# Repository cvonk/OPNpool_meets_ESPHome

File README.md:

> OPNpool Meets ESPHome has been merged with my [original OPNpool](https://github.com/cvonk/OPNpool) repo.  Please refer to that repo instead.

Ever dreamed of making your pool smarter and easier to manage? If you’ve ever owned a backyard pool, you know it’s not just about swimming—there’s a whole world of chemicals, covers, vacuums, brushes, and fiddling with thermostats and circuits. Even with a saltwater pool, you’ve got to keep a close eye on things!

Enter OPNpool: your pool’s new best friend. It takes all the classic pool controller features and brings them into your smart home. OPNpool keeps track of your controller, pump, and chlorinator, so you don’t have to run outside every time you want to check or change something. Even better, you can set up automations—like running the pump longer when it’s hot out—all from the comfort of your phone or smart home dashboard.

Thanks to some clever folks who reverse engineered the RS485 protocol, OPNpool can eavesdrop on the chatter between your pool’s components. The ESP32 inside shares all that state info as JSON/HTTP and can publish it via MQTT. And if you’re a Home Assistant fan, you’ll love how easily it integrates using MQTT Discovery.

# OPNpool meets ESPHome

OPNpool meets ESPHome is an open-source hardware and software solution that brings advanced pool automation to your smart home. By bridging legacy pool controllers with modern IoT platforms, OPNpool enables real-time monitoring, remote control, and seamless integration with Home Assistant. Whether you want to automate your pool pump based on temperature, monitor chlorinator status, or simply enjoy the convenience of remote access, OPNpool provides a robust and extensible platform for pool management.

## How it works

At its core, OPNpool connects an ESP32 microcontroller to your pool controller’s RS-485 bus. The ESP32 runs ESPHome firmware, which translates pool equipment data into Home Assistant entities. This allows you to view and control your pool’s thermostats, pumps, circuits, and chlorinator directly from your smart home dashboard or mobile app. The system is designed for reliability, safety, and ease of installation, with support for over-the-air updates and waterproof enclosures for outdoor use.

## Features

- [x] **Smart Home Integration:** Native support for Home Assistant and ESPHome.
- [x] **Remote Monitoring & Control:** Access your pool’s status and controls from anywhere.
- [x] **Community Driven:** Built on the work of pool automation enthusiasts and reverse engineers.
- [x] **Open Source:** Fully transparent hardware and software—customize and extend as needed.

## Getting started

No prior experience with pool automation or ESPHome is required. The documentation below will guide you through hardware assembly, wiring, firmware installation, and Home Assistant integration. If you have questions or need help, join the project’s GitHub Discussions for community support.

This device was tested with the Pentair SunTouch controller with firmware **2.080** (2013-07-15), connected to an IntelliFlo pump and IntelliChlor saltwater chlorinator.

> This open source and hardware project is intended to comply with the October 2016 exemption to the Digital Millennium Copyright Act allowing "good-faith" testing," in a controlled environment designed to avoid any harm to individuals or to the public.

## Acknowledgements

> We proudly acknowledge the work of reverse engineering pioneers [Joshua Bloch](https://docs.google.com/document/d/1M0KMfXfvbszKeqzu6MUF_7yM6KDHk8cZ5nrH1_OUcAc/edit), [Michael Russe](http://cocoontech.com/forums/files/file/173-pab014sharezip/), and [George Saw](http://cocoontech.com/forums/topic/27864-download-pitzip/). (Drop me a line if I forgot you.)

## Usage

Start with [installing the ESPHome environment](https://esphome.io/guides/installing_esphome/) on a beefy computer. In my case, this cut the compilation time to a minute, compared to half an hour when running it as an add-on to Home Assistant.

In an empty directory, create a `opnpool-1.yaml` configuration file as shown below.
```yaml
substitutions:
  device_name: opnpool-1
  friendly_name: "OPNpool meets ESPHome"
  description: "External component, see https://github.com/cvonk/OPNpool_meets_ESPHome"

esphome:
  name: ${device_name}
  comment: ${description}
  friendly_name: ${friendly_name}

esp32:
  variant: esp32c6          # or esp32     for <= r3 boards
  board: esp32-c6-devkitc-1 # or lolin_d32 for <= r3 boards
  framework:
    type: esp-idf

wifi:
  domain: !secret domain_name # only needed if not on the same subnet
  min_auth_mode: WPA2
  reboot_timeout: 0s
  networks:
  - ssid: !secret wifi_ssid
    password: !secret wifi_password

api:

ota:
  - platform: esphome
    password: !secret ota_password

external_components:
  - source: github://cvonk/OPNpool_meets_ESPHome
    components: [ opnpool ]

logger:
  level: VERBOSE          # build includes ESP_LOGx up to VERBOSE
  initial_level: WARN     # only show up to WARN globally
  logs:
    poolstate_rx: VERBOSE # show decoded messages

opnpool:
  id: opnpool_1
  RS-485:
    tx_pin:  21  # or 26 for <= r3 boards 
    rx_pin:  22  # or 25 for <= r3 boards
    rts_pin: 23  # or 27 for <= r3 boards
```

Specify your own secrets in `secrets.yaml`

```yaml
wifi_ssid: "REDACTED"
wifi_password: "REDACTED"
domain_name: ".iot.example.com" # appended to base fname to create FQDN for OTA updates
ota_password: "REDACTED"
api_encryption_key: "REDACTED"
```

Compile and upload the code using

```bash
esphome run opnpool-1.yaml
```

The first time, you need to upload over USB Serial, but after that you can use over-the-air updates.

In the output, you should see something like:

```text
[16:26:54.983]I (423) boot: Loaded app from partition at offset 0x10000
[16:26:55.024]I (465) boot: Set actual ota_seq=1 in otadata[0]
[16:26:55.029]I (465) boot: Disabling RNG early entropy source...
[16:26:55.268][W][component:333]: api set Warning flag: unspecified
[16:26:55.273][W][component:342]: wifi set Warning flag: scanning for networks
[16:27:01.293][W][component:373]: wifi cleared Warning flag
[16:27:25.143][E][RS-485:108][pool_req_task]: tx_q full
[16:27:55.144][E][RS-485:108][pool_req_task]: tx_q full
```

In the above trace, the `tx_q full` indicates that it can't transmit to the pool controller.

If you haven't already, add the ESPHome integration to Home Assistant.

Under Integrations, you will find now notice that Home Assistant auto discovered your new device.

{: style="display: block; margin-left: auto; margin-right: auto; width:300px;}

Add it, and specify your API key.  Name the device and assign it an area. You should then see the enities although their values are `unknown`.  Time to populate those entities by connecting it to the pool controller ;-)

## Connect

At the core this project is an ESP32 module and a 3.3 Volt RS-485 adapter. You can
breadboard this using:

* Any ESP32 module that has an USB connector and three GPIO pins available.
* Any "Max485 Module TTL". To make it 3.3 Volt compliant, change the chip to a `MAX3485CSA+`. While you're at it, you may as well remove the 10 kΩ pullup resistors (typically labeled `R1` to `R4`).
* A piece of Cat5 ethernet cable to connect to the pool controller.

{: style="display: block; margin-left: auto; margin-right: auto; width:300px;}

If you prefer to make this a more permanent solution, I suggest rolling a printed circuit board and housing it in a IP68 waterproof case with IP68 connectors.  More about this later.

> :warning: **THIS PROJECT IS OFFERED AS IS. IF YOU USE IT YOU ASSUME ALL RISKS. NO WARRANTIES. At the very least, turn off the power while you work on your pool equipment. Be careful, THERE IS ALWAYS A RISK OF BREAKING YOUR POOL EQUIPMENT.**

Understanding the above warning .. the RS-485 header can be found on the back of the control board. There are probably already wires connected that go to the devices such as pump and chlorinator.

{: style="display: block; margin-left: auto; margin-right: auto; width:400px;}

To minimize electromagnetic interference, use a twisted pairs from e.g. CAT-5 cable to connect the `A`/`B` pair to the RS-485 adapter as shown in the table below.

| Controller       | RS-485 adapter | idle state |         
|:-----------------|:--------------:|:-----------|
| `-DATA` (green)  |  `A`           | negative   |
| `+DATA` (yellow) |  `B`           | positive   |

Connect the RS-485 adapter to the ESP32 module.  I also pulled `GPIO#27` down with a 10 k&ohm; resistor, to keep it from transmiting while the ESP32 is booting.

| RS-485 adapter | ESP32 module |
|:---------------|:-------------|
| RO             | `GPIO#25`    |
| DI             | `GPIO#26`    |
| DE and RE      | `GPIO#27`    |
| GND            | `GND`        |

The serial monitor will start to show decoded messages such as:

```json
{CTRL_VERSION_REQ: {}}
{CTRL_VERSION_RESP: {"firmware":"2.80"}}
{CTRL_TIME_REQ: {}}
{CTRL_TIME_RESP: {"tod":{"time":"18:51","date":"2026-01-18"}}}
{CTRL_HEAT_REQ: {}}
{CTRL_HEAT_RESP: {"thermos":{"POOL":{"temp":54,"sp":63,"src":"NONE"},"SPA":{"temp":54,"sp"}
```

> :bulb: If you don't see such messages, make sure you didn't swap the data leads, or oddly enough some people report that they do need to swap the data leads.  To debug the datalink framing, set the `datalink_rx` logger level to `VERBOSE` and build and upload the code again. See futher below.

In Home Assistant the entities should populate, and show on your favorite Lovelace UI.

{: style="display: block; margin-left: auto; margin-right: auto; width:500px}

## PCB

For a robust and weatherproof installation, we recommend building a custom printed circuit board (PCB) to house the ESP32-C6 module, RS-485 adapter, and DC/DC converter. This approach ensures reliable connections, easier mounting, and long-term durability—especially for outdoor or poolside environments.

{: style="display: block; margin-left: auto; margin-right: auto; width:500px}

Note that the photo above is from a rev 1 board.

### Schematic

The hardware design features a buck converter that supplies 5V to the `5V0` pin on the ESP32-C6 DevKitC-1-N8 daughterboard. The scotty diode prevent issues when the board is also powered via USB.

The main data path runs between the RS-485 connector and the ESP32-C6 on the DevKitC-1-N8. An optional termination resistor is included to minimize signal reflections on the RS-485 bus.

### Board Layout

The entire schematic fits comfortably on a compact two-layer PCB. The board was designed using the free version of AutoDesk EAGLE, and all source files — including layout and schematics — are available in the [hardware directory](tree/main/hardware) of this repository.

{: style="display: block; margin-left: auto; margin-right: auto;}

### Bill of materials

| Name        | Description                                              | Suggested mfr/part#        | Price paid
|-------------|----------------------------------------------------------|----------------------------|-----------
| PBC r4      | Printed circuit board                                    | OSHPark                    | [$9.43](https://oshpark.com/)
| Enclosure   | 158x90x60mm ABS Plastic Junction Box, IP65               | *white label*              | [$9.81](https://www.harfington.com/products/p-1159792)
| RS-485_CONN | 5P Plug+socket, 5-pin, 16mm aviation, IP68               | SP16 5P                    | [$3.98](https://www.aliexpress.us/item/2251832722757291.html)
| RS-485-TERM | Fixed terminal block, 4-pin, screwless, 5 mm pitch       | Phoenix-Contact 1862437    | [$2.02](https://www.digikey.com/en/products/detail/phoenix-contact/1862437/6605421)
| ESP32-C6 DevKitC-1-N8 | ESP32-C6 dev board with 8MB flash, based on ESP32-C6-WROOM | ESP32-C6 DevKitC-1-N8      | [$9.00](https://www.digikey.com/en/products/detail/espressif-systems/ESP32-C6-DEVKITC-1-N8/17728861)
| MAX3485     | Maxim MAX3485CSA, RS-485/UART interface IC 3.3V, 8-SOIC  | Analog-Devices MAX3485CSA+T | [$5.64](https://www.digikey.com/en/products/detail/analog-devices-inc-maxim-integrated/MAX3485CSA-T/1703654)
| DC1         | DC/DC Converter R-78E5.0-0.5, 7-28V to 5V, 0.5A, 3-SIP   | RECOM-Power R-78E5.0-0.5   | [$3.30](https://www.digikey.com/en/products/detail/recom-power/R-78E5-0-0-5/2834904?s=N4IgTCBcDaIEoFEDCB5AsgWgAoHsDuApgE4AEcGA7ABwICsAdAAwaP20gC6AvkA)
| D1, D2      | Schottky Diode, 1N5818, 30V, 1A, DO-41                   | Diodes Incorporated 1N5818-T | [$0.30](https://www.digikey.com/en/products/detail/diodes-incorporated/1N5818-T/22054)
| LED1        | LED, Green Clear 571nm, 1206                             | Lite-On LTST-C150KGKT       | [$0.15](https://www.digikey.com/en/products/detail/diodes-incorporated/1N5818-T/22054)
| LED2        | LED, Amber Clear 602nm, 1206                             | Lite-On LTST-C150AKT       | [$0.15](http2s://www.digikey.com/en/products/detail/liteon/LTST-C150AKT/269213?s=N4IgTCBcDaIDIEsAuBTAtAeQHYAI4BUBlfNAYQEYBWABgEEBpfEAXQF8g)
| C1, C2      | Capacitor, 10 µF, 25 V, multi-layer ceramic, 0805        | KEMET C0805C106K3PACTU     | [$0.22](https://www.digikey.com/en/products/detail/kemet/C0805C106K3PACTU/5267604?s=N4IgTCBcDaINIFECyCAqACAwgBgBzYFZMBGbANjgGYAFAQU1QFUQBdAXyA)
| C3          | Capacitor, 0.1 µF, 6.3 V, multi-layer ceramic, 0805      | KEMET C0805C104M3RACTU     | [$0.12](https://www.digikey.com/en/products/detail/kemet/C0805C104M3RACTU/2211748?s=N4IgTCBcDaINIFECyCAqACAwgBgBzYFZMBGbAFiQGYAlAQU1QFUQBdAXyA)
| R1, R2      | Resistor, 68 Ω, 1/8 W, 0805                              | YAGEO RC0805FR-0768RL      | [$0.20](https://www.digikey.com/en/products/detail/yageo/RC0805FR-0768RL/728097?s=N4IgTCBcDaIJoEEDiBRA8gAgEoGEAMAHHgKwBiWAtHgOwBsBWAMiALoC%2BQA)
| R3          | Not stuffed, resistor, 120 Ω, 1/4 W, 0805                | KAO SG73S2ATTD121J         | [$0.00](https://www.digikey.com/en/products/detail/koa-speer-electronics-inc/RK73B2ATTD121J/10236600)
| PCB Screws  | Machine screw, #6-32 x x 3/16", panhead                  | Keystone-Electronics 9306  | [$0.10](https://www.digikey.com/en/products/detail/keystone-electronics/9306/2746085?s=N4IgjCBcpgTB0QGMoDMCGAbAzgUwDQgD2UA2iLAAwCsIAuoQA4AuUIAyswE4CWAdgHMQAX2GFYZEAGlcAT2zMifXAFoAoplxJuSnkmwACAJwBmSgDZ6woA)
| CONN Screws | Machine screw, M2-0.4 x 16 mm, cheese head               | Essentra 50M020040D016     | [$0.28](https://www.digikey.com/en/products/detail/essentra-components/50M020040D016/11639297)
| CONN Nuts   | Hex nut, M2-0.4, nylon                                   | Essentra 04M020040HN       | [$0.15](https://www.digikey.com/en/products/detail/essentra-components/04M020040HN/9677098)

Note that tariffs and shipping will add to the cost.

## Troubleshooting

Not all controller firmwares are created equally.  If you are not using firmware version 2.080, you will need dive down to the byte level and to tweak the network layer.  If you succeed, please send me an pull request, and I will iinclude it in the next release.

To show more (or less) debug information, specify the levels in `opnpoool-1.yaml`

```yaml
logger:
  level: VERBOSE       # build includes ESP_LOGx up to VERBOSE
  initial_level: WARN  # only show up to WARN globally
  logs:
    rs485: WARN
    datalink_rx: WARN
    datalink_tx: WARN
    network_rx: WARN
    network_create: WARN
    pool_task: WARN
    ipc: WARN
    poolstate: WARN
    poolstate_rx: VERBOSE
    opnpool: WARN
    opnpool_climate: WARN
    opnpool_switch: WARN
    opnpool_sensor: WARN
    opnpool_binary_sensor: WARN
    opnpool_text_sensor: WARN
    enum_helpers: WARN
```

For the `logger` component, it is recommended to use the following levels: `WARN`, which shows only warnings and errors; `INFO`, which includes informational messages such as configuration details, warnings, and errors; and `VERBOSE`, which provides very detailed logs, info, warnings, and errors. Be careful not to enable too much logging, as excessive output can negatively impact the connection between Home Assistant and the ESP32-C6.

### Decoding Stack Traces

If your ESP32-C6 crashes and you notice stack traces in the serial log, you can simplify debugging by enabling ESPHome's stack trace decoder. With this feature, exception addresses are automatically translated into human-readable function names and line numbers within your logs.

To activate the stack trace decoder, add the following lines to your YAML configuration:

```yaml
debug:
  update_interval: 5s  # for exception decoding in logs
```

> **Tip:** Detailed crash information will only appear on the serial console (not in the web logs). Be sure to check the serial output for troubleshooting.

# FAQ

**LEDs not blinking with RS-485 connected**

If communication fails, swap the `-DATA` and `+DATA` wires, as standards for these labels vary. 

**Is a controller required?**

This setup ensures that when selling the house, the next owner is not stuck with a "custom" system. They can use the pool conventionally or easily adopt the smart features.  If you're determined to build your own controller, I can recommend Russ Goldin's [nodejs-poolController](https://github.com/tagyoureit/nodejs-poolController/tree/master).

**Will it work with ___ board?**

There are many boards and kits that incorporate the ESP32. I started with the ESP8266, switched to the original ESP32, and use the ESP-C6. At this point it probably runs on any ESP32 flavor board. If you want to try something else, sure feel free the code is written to be portable. Just make sure you use the MAX3485 instead of the TTL-level MAX485.

**My firmware is ___ How do you update SunTouch firmware?**

Instead of taking such a risky step, I recommend enabling `VERBOSE` logging for `datalink_rx` and `network_rx`.  This will visualize the raw bytes received and messages interpretated. Compare that with the structures `network_msg.h`, and update the file as needed.

> Only do this if you very confident with flashing electronics. You risk bricking your pool controller.

Having read the above warning, you can upgrade if your controller is at [version 2.x](https://saturationregion.blogspot.com/2020/01/whats-deal-with-easytouch-versions-1.html). You will need to get a [USBDM JS16](https://www.aliexpress.us/w/wholesale-Freescale-USBDM-Programmer-JS16.html?spm=a2g0o.detail.search.0) programmer, [make](https://www.troublefreepool.com/threads/how-to-perform-firmware-upgrade-on-pentair-controllers.69589/#post-595657) a [JST cable](https://www.aliexpress.us/w/wholesale-5-PCS-JST-1.-25mm-Male-Female-6p.html?spm=a2g0o.detail.search.0) following [the instructions](https://www.troublefreepool.com/threads/how-to-perform-firmware-upgrade-on-pentair-controllers.69589/page-7#post-2021911).

#
I hope this project brings you joy.  Keep in touch through the dicussion forum.

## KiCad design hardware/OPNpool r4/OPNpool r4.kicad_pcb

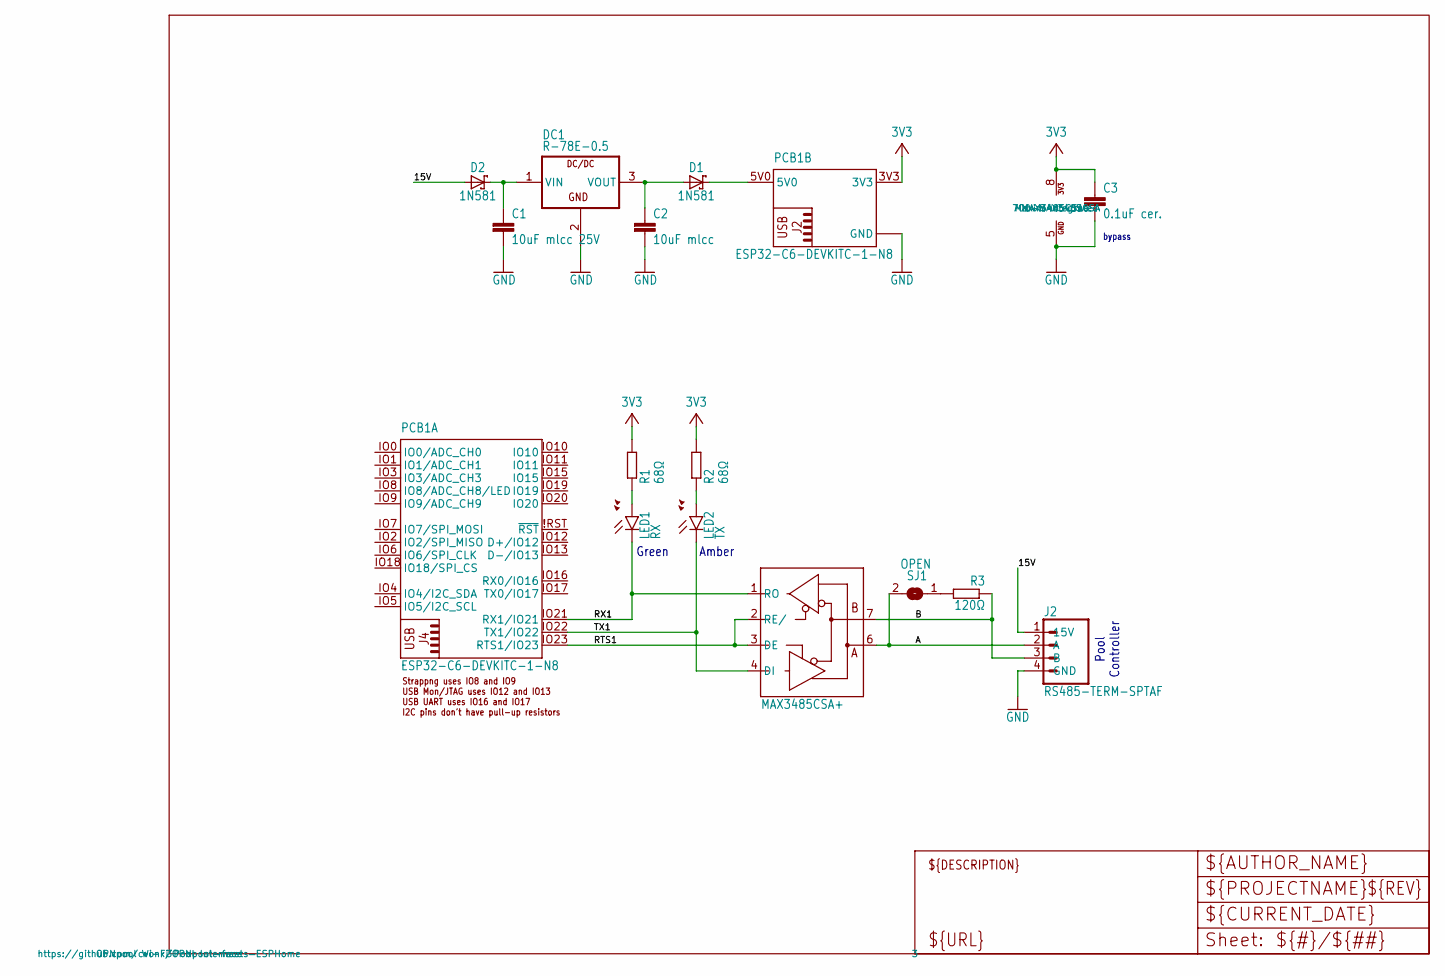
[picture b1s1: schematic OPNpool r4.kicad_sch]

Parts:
C1: 10uF mlcc 25V; C0805K; MOUSER# 81-GJ821BR61E106KE1L
C2: 10uF mlcc; C0805K; MOUSER# 81-GJ821BR61E106KE1L
C3: 0.1uF cer.; C0805K; MOUSER# 80-C0805C104K1REAUTO
D1, D2: 1N581; DO41-7.6; MOUSER# 583-1N5818-T
DC1: R-78E-0.5; SIP3; MOUSER# 919-R-78E5.0-0.5
J2: RS485-TERM-SPTAF; SPTAF1_4-5,0-LL; MOUSER# 651-1864451
LED1: RX; CHIPLED_0805
LED2: TX; CHIPLED_0805
PCB1: ESP32-C6-DEVKITC-1-N8; MODULE_ESP32-C6-DEVKITC-1-N8
R1, R2: 68Ω; R0805; MOUSER# 652-CRM0805JW1R5ELF
R3: 120Ω; R0805; MOUSER# 652-CRM0805JW1R5ELF
SJ1: OPEN; SJ
U1: MAX3485CSA+; SO08; MOUSER# 700-MAX3485CSA

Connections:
3V3: C3.1, PCB1.3V3, R1.2, R2.2, U1.8 (VCC)
15V: D2.A, J2.1 (15V)
A: J2.2 (A), SJ1.2, U1.6 (A)
B: J2.3 (B), R3.1, U1.7 (B)
GND: C1.2, C2.2, C3.2, DC1.2 (GND), J2.4 (GND), PCB1.GND, PCB1.GND@1 (GND), PCB1.GND@2 (GND), PCB1.GND@3 (GND), U1.5 (GND)
unnamed: LED1.A, R1.1
unnamed: LED2.A, R2.1
unnamed: D1.C, PCB1.5V0
unnamed: R3.2, SJ1.1
RTS1: PCB1.IO23 (RTS1/IO23), U1.2 (RE/), U1.3 (DE)
RX1: LED1.C, PCB1.IO21 (RX1/IO21), U1.1 (RO)
TX1: LED2.C, PCB1.IO22 (TX1/IO22), U1.4 (DI)
VIN: C1.1, D2.C, DC1.1 (VIN)
VOUT: C2.1, D1.A, DC1.3 (VOUT)

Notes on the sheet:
bypass
Pool Controller
Green
Amber

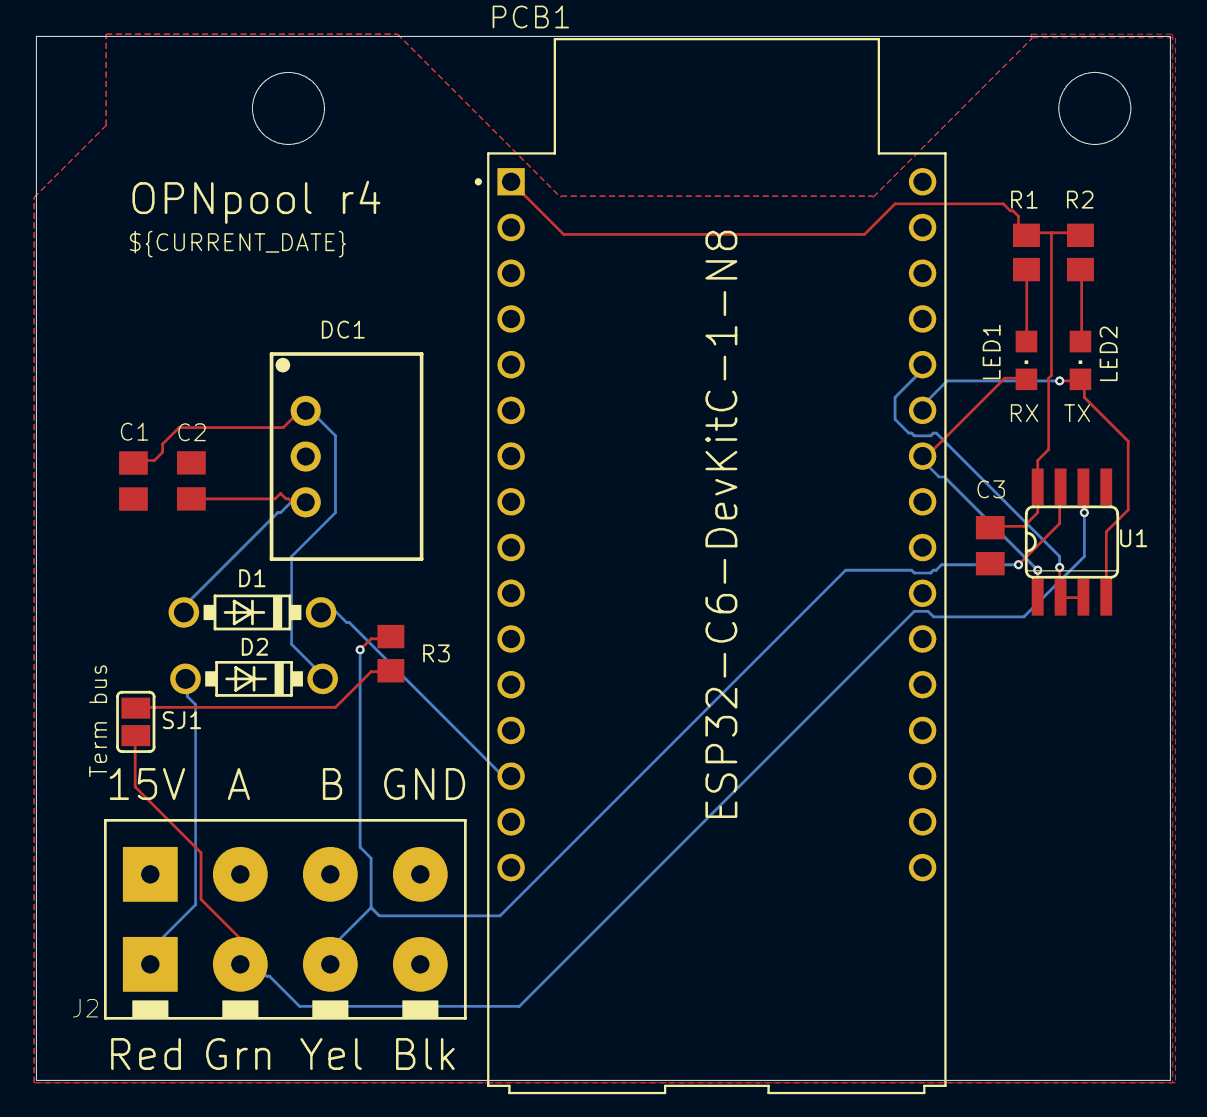
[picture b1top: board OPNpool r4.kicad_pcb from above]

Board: 2 copper layers, 63.0 x 58.0 mm, 17 parts (0 on the bottom side), 14 nets.

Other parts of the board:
UNK_HOLE_0: dummyfp0
UNK_HOLE_1: dummyfp1

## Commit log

2025-12-30 Create README.md for OPNpool project
    Add initial README for OPNpool project with features and setup instructions.
2026-01-03 initial
2026-01-03 add entities
2026-01-03 one more step
2026-01-03 use native UART
2026-01-03 add device class to analog sensors
2026-01-03 add debug levels
2026-01-04 add missing entities
2026-01-04 first bytes received
2026-01-04 group debug keys
2026-01-05 add dbg levels
2026-01-05 Stop tracking __pycache__ directory
2026-01-06 import modules from my regular OPNpool project
2026-01-06 initial msg from pool ctrl
2026-01-06 log msgs from datalink_rx.cpp are now showing up after adding the apparently missing #include "esphome/core/log.h"
2026-01-06 move debug settings to logger
2026-01-06 refractor
2026-01-06 fix crash in case IPC_TO_HOME_TYP_PUBLISH_DATA_DBG
2026-01-07 prevent *(null) read, by change network_msg_t to have a bytes[0] member instead of *bytes.
2026-01-07 prep for moving poolstate to home_task
2026-01-07 add doxygen blocks for skb
2026-01-07 fix skb_pull()
2026-01-08 use correct include paths to help intilisense
2026-01-08 make network_msg the interface between the home and pool tasks
2026-01-08 fix compile err
2026-01-08 fix debug statements
2026-01-08 Initial plan
2026-01-08 Implement IPC switch command forwarding to pool_task
    - Extended OpnPoolSwitch with parent pointer and circuit_id
    - Implemented OpnPool::on_switch_command() to allocate and send network_msg_ctrl_circuit_set_t via IPC
    - Updated pool_task to handle MSG_TYP_CTRL_CIRCUIT_SET messages and convert to datalink packets
    - Wired up switches in __init__.py with parent and circuit_id mapping
2026-01-08 Add initial README for OPNpool porting project
2026-01-08 Update README with project link for OPNpool
2026-01-09 undo a bunch of Copilot PR. First time setting circuit works
2026-01-09 simplify IPC msg to pool_task
2026-01-09 add notes about X-macros
2026-01-09 fix compile err re str_value_name_pair_t
2026-01-09 simplify IPC msg to main_task
2026-01-09 made poolstate a class
2026-01-09 reduce log msgs
2026-01-09 reduce logs further
2026-01-09 update ©- statements
2026-01-09 update SPDX-FileCopyrightText
2026-01-09 move tmp files out of the way
2026-01-09 add magic enum support
2026-01-09 switch DATALINK_ADDRGROUP to magic enum
2026-01-10 Replace many X-macros with magic enums. Replace COUNT enum members with inline function. Specify build tasks that adjust the file path in he vscode Problems tab.
2026-01-10 fix sizeof(empty struct) == 1
2026-01-11 no longer needed
2026-01-11 Fix A5_PUMP prot_typ=STATUS: expected data_len=1, got data_len=0
2026-01-11 fix sizeof(network_msg_pump_status_req_t) to 0
2026-01-11 rename network_typ_t to datalink_typ_t
2026-01-11 check return type from network_msg_typ_get_info()
2026-01-11 clean circular #includes
2026-01-11 winter cleaning
2026-01-11 move compile flags to __init__.py
2026-01-11 fix circular #includes
2026-01-11 include cstddef where needed
2026-01-11 fix intellisense errors
2026-01-11 work around intellisense limitations
2026-01-12 add logic to report "switch changed" back to HA
2026-01-12 add other sensors to report to HA
2026-01-12 add climate reporting from pool
2026-01-12 added HA setting thermostats
2026-01-12 make HA send the temp in F (instead of C)
2026-01-12 convert temp where needed. ESPHome uses C internally; the pool ctrl uses F.
2026-01-12 for thermostats, handle mode changes
2026-01-12 group classes into arrays
2026-01-12 change year to 4 digits
2026-01-13 rm pump_status, aux1_sched, aux2_sched. rm opnpoolstate_get.cpp. rm poolstate_elem_modes_typ_t
2026-01-13 add interface firmware version
2026-01-13 make all yaml parameters/keys optional
2026-01-13 rm uart dependency
2026-01-13 correct opnpool id
2026-01-13 move entities from openpool.c to their own files
2026-01-14 fix schedule reporting, and climate entities
2026-01-14 stronger type checking
2026-01-14 work towards a minimal config yaml
2026-01-14 stronger type checks
2026-01-14 update Doxygen blocks
2026-01-14 document more details in doxygen blocks
2026-01-14 refractor, to minimize the data length validation logic in each decoder function.
2026-01-15 clearn up publish_value_if_changed() methods
2026-01-15 generate opnpool.h enums from __init__.py
2026-01-15 use helper function to convert enum class to its underlying type
2026-01-15 add dods
2026-01-15 using instead of typedef
2026-01-15 cleanup and document
2026-01-16 use uint8_str instead of static char[]. Introduce templated enum_str fnc
2026-01-16 templated enum *_str, *_nr and *_count
2026-01-16 move enum helpers to their own file
2026-01-16 update comments
2026-01-16 reduce boilerplate
2026-01-16 less boilerplate
2026-01-16 change typedef to using
2026-01-17 more comments. more defensive.
2026-01-17 check for old state being initialized
2026-01-17 cleanup
2026-01-17 more checks
2026-01-17 more cleanup
2026-01-17 follow review suggestions
2026-01-17 refractor. extend comments
2026-01-17 move _ic_type_len_table[] back to function, 'cause enum is non-continuous.
2026-01-17 move state comparision from opnpool_state_rx
2026-01-18 spin off opnpool_state_rx.h and opnpool_state_log
2026-01-18 reorder namespace opnpool_state_log
2026-01-18 add comment
2026-01-18 rename opnpool_state.h to pool_stae.h
2026-01-18 rename files
2026-01-18 make for() loopsover enums more elegant
2026-01-18 remove COUNT from generated enum classes to fix OOB exception.
2026-01-18 rm unneeded commas
2026-01-19 add documentation
2026-01-19 fix image paths
2026-01-19 correct image path
2026-01-19 replace img
2026-01-19 add img
2026-01-19 add pkg
2026-01-19 correct spell err
2026-01-19 update dep
2026-01-19 update license
2026-01-19 map the mapping from SwitchId to network_circuit explicit
2026-01-19 map the mapping from ClimateId to poolstate_thermos_typ explicit
2026-01-19 more sanity checks
2026-01-19 remove dead code
2026-01-19 add comments
2026-01-19 extend dump_config
2026-01-19 tweak dump_config
2026-01-19 move ids to its own files
2026-01-19 more type checking
2026-01-19 cleanup last_.valid
2026-01-19 rm unneeded id_
2026-01-19 combine the two heat_src defs
2026-01-19 use helper functions for clarity
2026-01-19 fix for not all switches not reporting back
2026-01-19 surpress freq broadcast msg
2026-01-20 fix dump of sensors
2026-01-20 formatting
2026-01-20 add lovelace img
2026-01-20 correct spell errs
2026-01-20 reduce dependencies
2026-01-20 add hardware
2026-01-20 rm obsolete
2026-01-20 rm unneeded
2026-01-20 rm #define
2026-01-21 rename pool_state to poolstate
2026-01-21 update w/ design info
2026-01-21 rm stray
2026-01-21 checkup on fnc proto and forward declarations
2026-01-21 rm dead code
2026-01-21 fix compile warnings at -Wall -Wextra level
2026-01-21 treat gcc warnungs as errors
2026-01-23 paranoid checks; start add granular valid to state
2026-01-23 more add granular valid to state
2026-01-23 more add granular valid to state cont'd
2026-01-24 final touches on adding granular valid to state
2026-01-26 switch to esp32-c6-devkitc-1 module
2026-01-26 switch to esp32-c6-devkitc-1 module #2
2026-01-26 cleanup poolstate_rx_log.cpp
2026-01-26 cleanup poolstate_rx_log.cpp #2
2026-01-27 cleanup poolstate_rx_log.cpp #3
2026-01-27 cleanup poolstate_rx_log.cpp #4
2026-01-27 create option for 2nd pump
2026-01-28 add no_disregards
2026-01-30 esp32c6 boards work. add return code checks.
2026-01-30 mv pump primary_pump; add cleanup; make single threaded more clear
2026-01-30 cleanuo
2026-01-30 cleanup network_msg_t
2026-01-30 make bit fields portable
2026-01-30 convert the network_msg_typ_t enum and its associated lookup tables to use the X-Macro pattern
2026-01-30 rm unneeded static_assert
2026-01-30 add note
2026-01-30 validate data len /before/ copying
2026-01-30 validate data len /before/ copying #2
2026-01-30 rm collosal switch() statements in network_rx; cleanup network_msg
2026-01-31 refractor; fix prevent memory leak on allocation failure
2026-01-31 refractor; introduce datalink_addr_t w/ get/set
2026-01-31 extend log statement
2026-02-01 add docs; refractor
2026-02-02 update docs
2026-02-02 Change badge link to ESPHome Discussions
    Updated badge link to point to ESPHome Discussions.
2026-02-02 Clean up README and add cost note
    Removed redundant HTML entities and added a note about costs.
2026-02-02 Fix grammar and formatting in README.md
    Corrected minor grammatical issues and formatting in the README.
2026-02-02 add files
2026-02-02 reshuffle; refractor
2026-02-02 prep for Matter over Thread support
2026-02-02 Thread network transport is working (when enabled in yaml). Mater is waiting for native ESPHome support.
2026-02-02 bump partitions
2026-02-04 fix typo
2026-02-04 rm stray comment
2026-02-04 introduce network_pool_modes_t
2026-02-04 less chatter
2026-02-05 update FAQ
2026-02-06 clean up pump msgs. refractor
2026-02-06 pass src/dst from datalink to network layer
2026-02-07 now learns the controller address from its bcast
2026-02-07 show year as 2026 instead of 0026
2026-02-07 store controller addr with poolstate instead
2026-02-07 change text state from controller_firmware to controller_type
2026-02-07 report ctrl system time as 2026 to HA (intead of 0026)
2026-02-07 correct water/air temp reported to HA
2026-02-07 change air temp sensor input
2026-02-07 move to sub dir, step 1
2026-02-07 move to sub dir, step 2
2026-02-08 move to sub dir, step 3
2026-02-08 move to sub dir, step 4
2026-02-08 move to sub dir, step last.
2026-02-11 move dirs

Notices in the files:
README.md:
License: GPL v3
